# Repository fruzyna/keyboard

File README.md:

# keyboard

Here I will put my keyboard development. I will attempt to tag each version I get printed. For the first version I used these libraries:
- https://github.com/keebio/keebio-components
- https://github.com/keebio/Keebio-Parts.pretty
- https://github.com/daprice/keyswitches.pretty

I then modded them to my liking for future versions.

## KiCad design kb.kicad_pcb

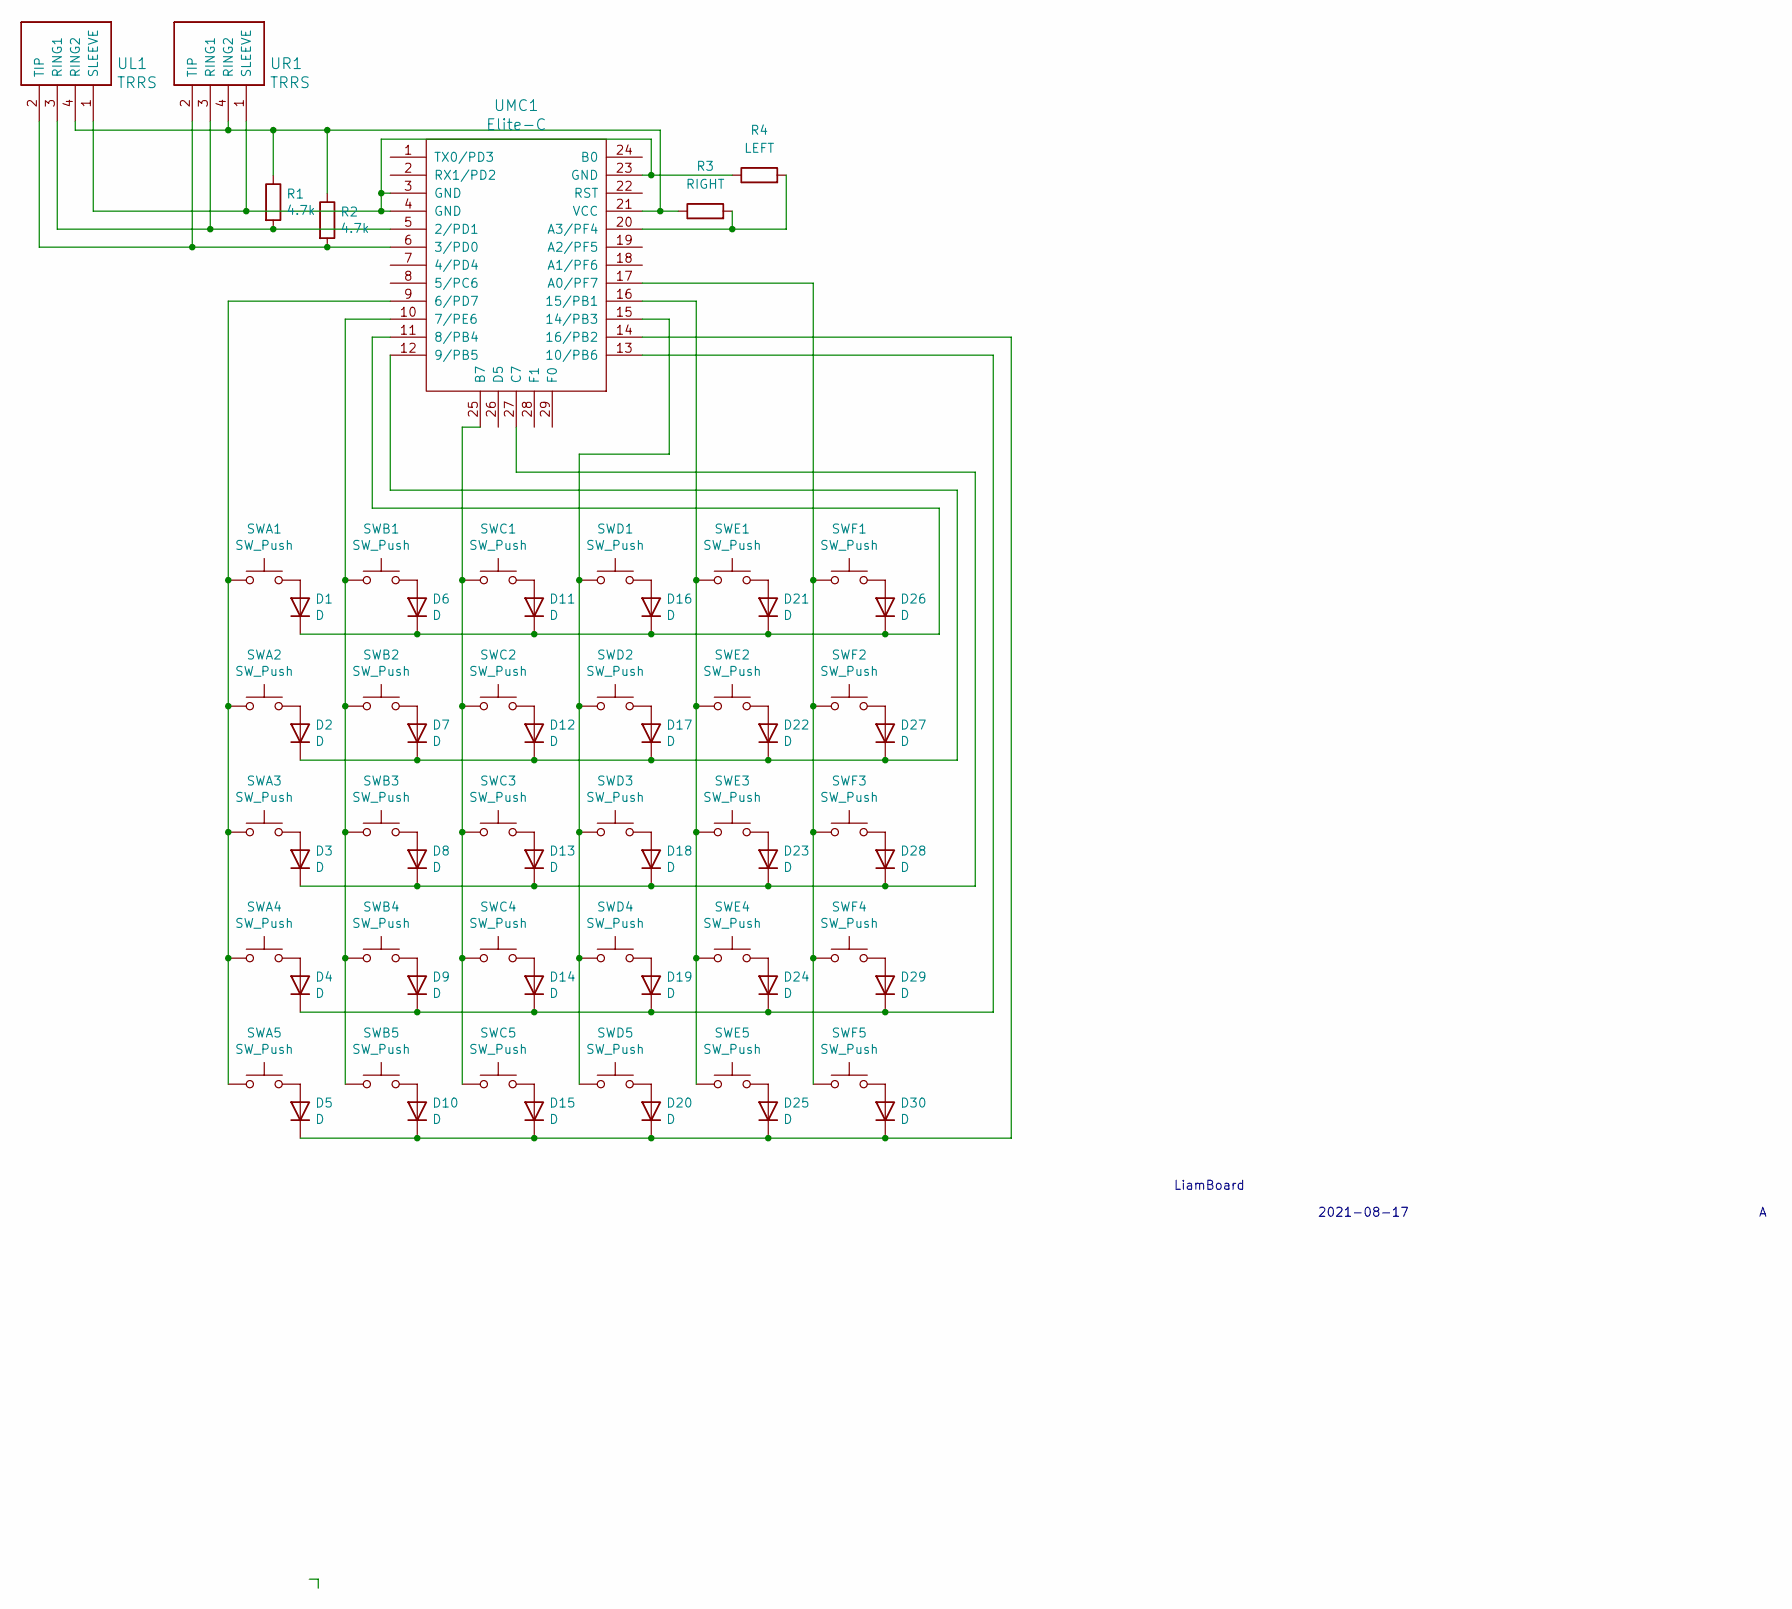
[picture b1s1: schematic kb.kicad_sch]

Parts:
D1, D2, D3, D4, D5, D6, D7, D8, D9, D10, D11, D12, D13, D14, D15, D16, D17, D18, D19, D20, D21, D22, D23, D24, D25, D26, D27, D28, D29, D30: D; Diode
R1, R2: 4.7k; R_Axial_DIN0207_L6.3mm_D2.5mm_P7.62mm_Horizontal
R3: RIGHT; SolderJumper-2_P1.3mm_Open_TrianglePad1.0x1.5mm
R4: LEFT; SolderJumper-2_P1.3mm_Open_TrianglePad1.0x1.5mm
SWA1, SWA2, SWA3, SWA4, SWA5: SW_Push; SW_MX_reversible
SWB1, SWB2, SWB3, SWB4, SWB5: SW_Push; SW_MX_reversible
SWC1, SWC2, SWC3, SWC4, SWC5: SW_Push; SW_MX_reversible
SWD1, SWD2, SWD3, SWD4, SWD5: SW_Push; SW_MX_reversible
SWE1, SWE2, SWE3, SWE4, SWE5: SW_Push; SW_MX_reversible
SWF1, SWF2, SWF3, SWF4, SWF5: SW_Push; SW_MX_reversible
UL1: TRRS; TRRS-PJ-320A
UMC1: Elite-C
UR1: TRRS; TRRS-PJ-320A

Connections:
unnamed: D1.2 (A), SWA1.2
unnamed: D1.1 (K), D6.1 (K), D11.1 (K), D16.1 (K), D21.1 (K), D26.1 (K), UMC1.11 (8/PB4)
unnamed: D2.2 (A), SWA2.2
unnamed: D3.2 (A), SWA3.2
unnamed: D4.2 (A), SWA4.2
unnamed: D5.2 (A), SWA5.2
unnamed: D6.2 (A), SWB1.2
unnamed: D7.2 (A), SWB2.2
unnamed: D8.2 (A), SWB3.2
unnamed: D9.2 (A), SWB4.2
unnamed: D10.2 (A), SWB5.2
unnamed: D5.1 (K), D10.1 (K), D15.1 (K), D20.1 (K), D25.1 (K), D30.1 (K), UMC1.14 (16/PB2)
unnamed: D11.2 (A), SWC1.2
unnamed: D12.2 (A), SWC2.2
unnamed: D2.1 (K), D7.1 (K), D12.1 (K), D17.1 (K), D22.1 (K), D27.1 (K), UMC1.12 (9/PB5)
unnamed: D13.2 (A), SWC3.2
unnamed: D3.1 (K), D8.1 (K), D13.1 (K), D18.1 (K), D23.1 (K), D28.1 (K), UMC1.27 (C7)
unnamed: D14.2 (A), SWC4.2
unnamed: D4.1 (K), D9.1 (K), D14.1 (K), D19.1 (K), D24.1 (K), D29.1 (K), UMC1.13 (10/PB6)
unnamed: D15.2 (A), SWC5.2
unnamed: D16.2 (A), SWD1.2
unnamed: D17.2 (A), SWD2.2
unnamed: D18.2 (A), SWD3.2
unnamed: D19.2 (A), SWD4.2
unnamed: D20.2 (A), SWD5.2
unnamed: D21.2 (A), SWE1.2
unnamed: D22.2 (A), SWE2.2
unnamed: D23.2 (A), SWE3.2
unnamed: D24.2 (A), SWE4.2
unnamed: D25.2 (A), SWE5.2
unnamed: D26.2 (A), SWF1.2
unnamed: D27.2 (A), SWF2.2
unnamed: D28.2 (A), SWF3.2
unnamed: D29.2 (A), SWF4.2
unnamed: D30.2 (A), SWF5.2
unnamed: R1.2, UL1.3 (RING1), UMC1.5 (2/PD1), UR1.3 (RING1)
unnamed 36: R1.1, R2.1, R3.1, UL1.4 (RING2), UMC1.21 (VCC), UR1.4 (RING2); also elsewhere on the board
unnamed 37: R4.1, UL1.1 (SLEEVE), UMC1.3 (GND), UMC1.4 (GND), UMC1.23 (GND), UR1.1 (SLEEVE); also elsewhere on the board
unnamed: R2.2, UL1.2 (TIP), UMC1.6 (3/PD0), UR1.2 (TIP)
unnamed: SWA1.1, SWA2.1, SWA3.1, SWA4.1, SWA5.1, UMC1.9 (6/PD7)
unnamed: SWB1.1, SWB2.1, SWB3.1, SWB4.1, SWB5.1, UMC1.10 (7/PE6)
unnamed: SWD1.1, SWD2.1, SWD3.1, SWD4.1, SWD5.1, UMC1.15 (14/PB3)
unnamed: SWE1.1, SWE2.1, SWE3.1, SWE4.1, SWE5.1, UMC1.16 (15/PB1)
unnamed: SWF1.1, SWF2.1, SWF3.1, SWF4.1, SWF5.1, UMC1.17 (A0/PF7)
unnamed 44: R3.2, R4.2, UMC1.20 (A3/PF4); also elsewhere on the board
unnamed: SWC1.1, SWC2.1, SWC3.1, SWC4.1, SWC5.1, UMC1.25 (B7)

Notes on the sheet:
2021-08-17
LiamBoard

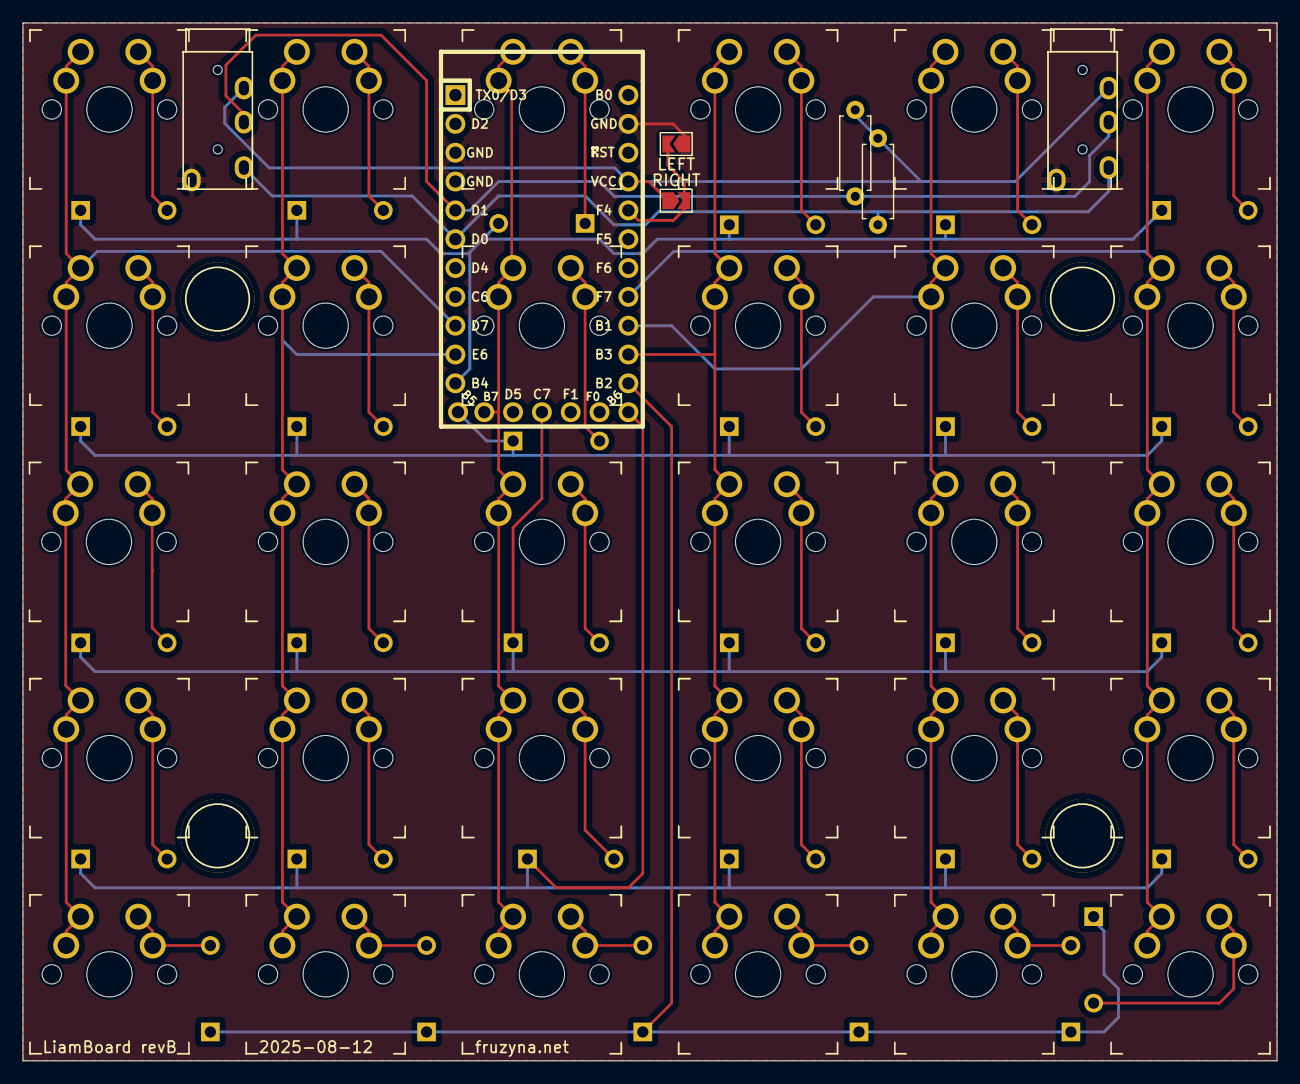
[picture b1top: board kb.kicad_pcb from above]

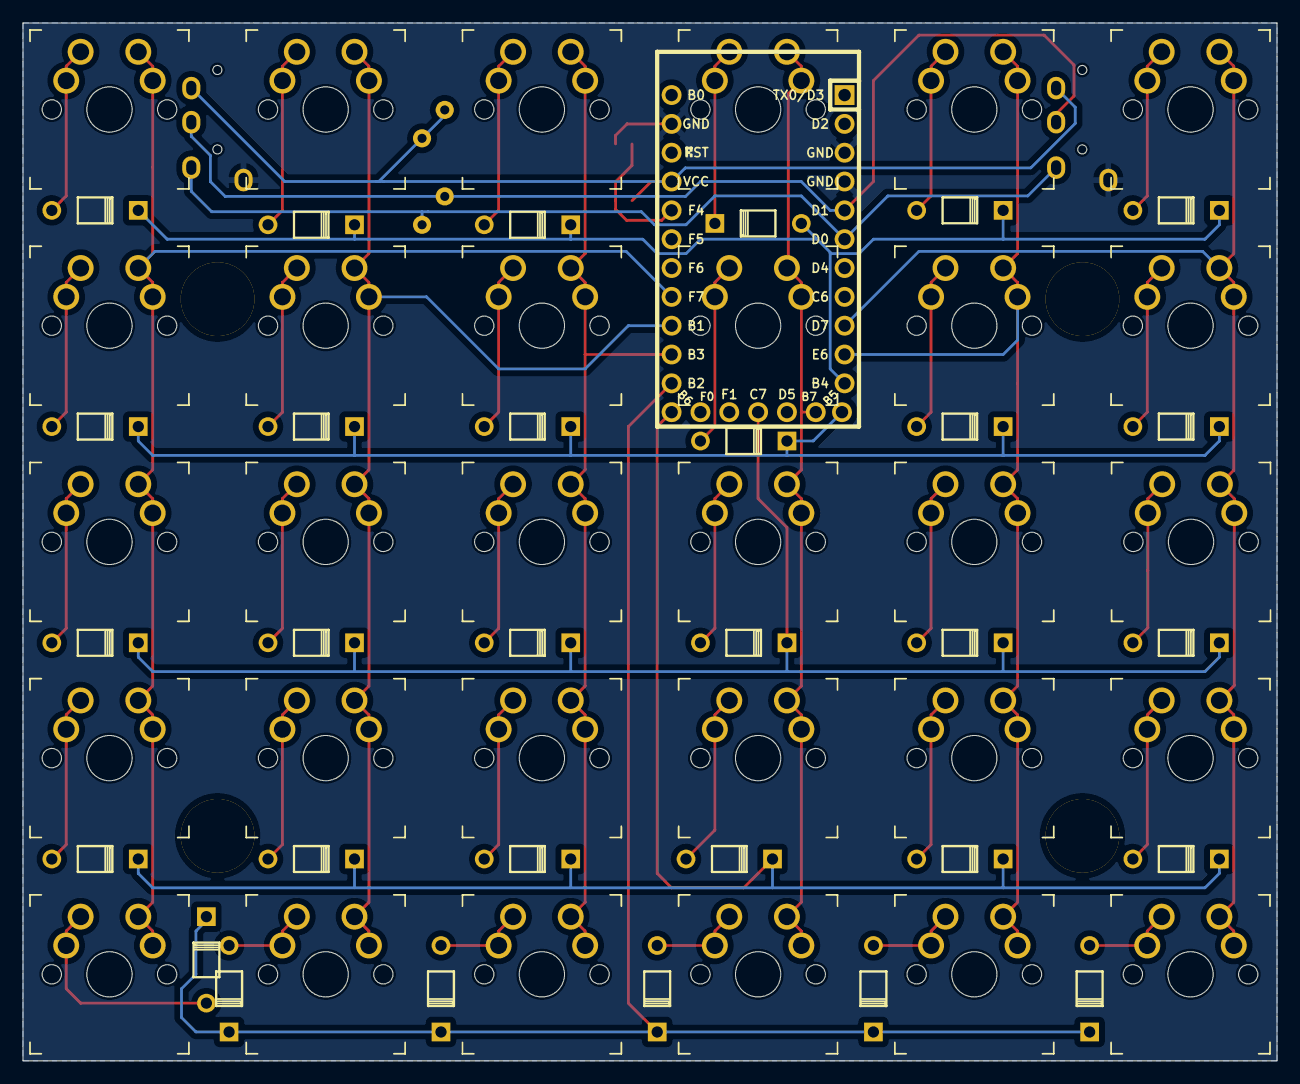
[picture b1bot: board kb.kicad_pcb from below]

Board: 2 copper layers, 110.5 x 91.4 mm, 71 parts (30 on the bottom side), 46 nets.

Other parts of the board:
LEFT: LEFT; SolderJumper-2_P1.3mm_Open_TrianglePad1.0x1.5mm
RIGHT: RIGHT; SolderJumper-2_P1.3mm_Open_TrianglePad1.0x1.5mm
U4, U4#2, U4#3, U4#4: HOLE; MountingHole

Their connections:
unnamed 36: RIGHT.1; also elsewhere on the board
unnamed 37: LEFT.1; also elsewhere on the board
unnamed 44: LEFT.2, RIGHT.2; also elsewhere on the board

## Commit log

2021-09-01 rev.A
2021-09-01 Fixed typo
2021-09-01 My adjusted versions of the footprints
2021-09-01 First (very rough) attempt at a layered case
2021-09-15 Fixed intersecting diode and trace (fixed #1)
2021-09-15 Shifted diode to improve fill
2021-09-17 Improved fill (fixed #2)
2021-09-18 Remade case to have proper key spacing
2021-09-21 Added PCB holes and mid-layers, decreased border width
2021-09-22 More screw holes and smarter rendering
2021-09-22 Prevent row-column overlapping
2021-10-03 Non-case mount
2021-10-04 Updated values based off real world measurements
2021-10-11 Mount tweaks
2021-10-12 Added pull up resistors for I2C
2022-08-26 What was on my pc before reset
2025-07-29 Updated diode footprint to simply be a reverse of the keebio footprint
2025-07-29 Fixed diode orientation (#3), added bridge points for left/right board, and other cleanup
2025-08-13 Silkscreen tweaks
